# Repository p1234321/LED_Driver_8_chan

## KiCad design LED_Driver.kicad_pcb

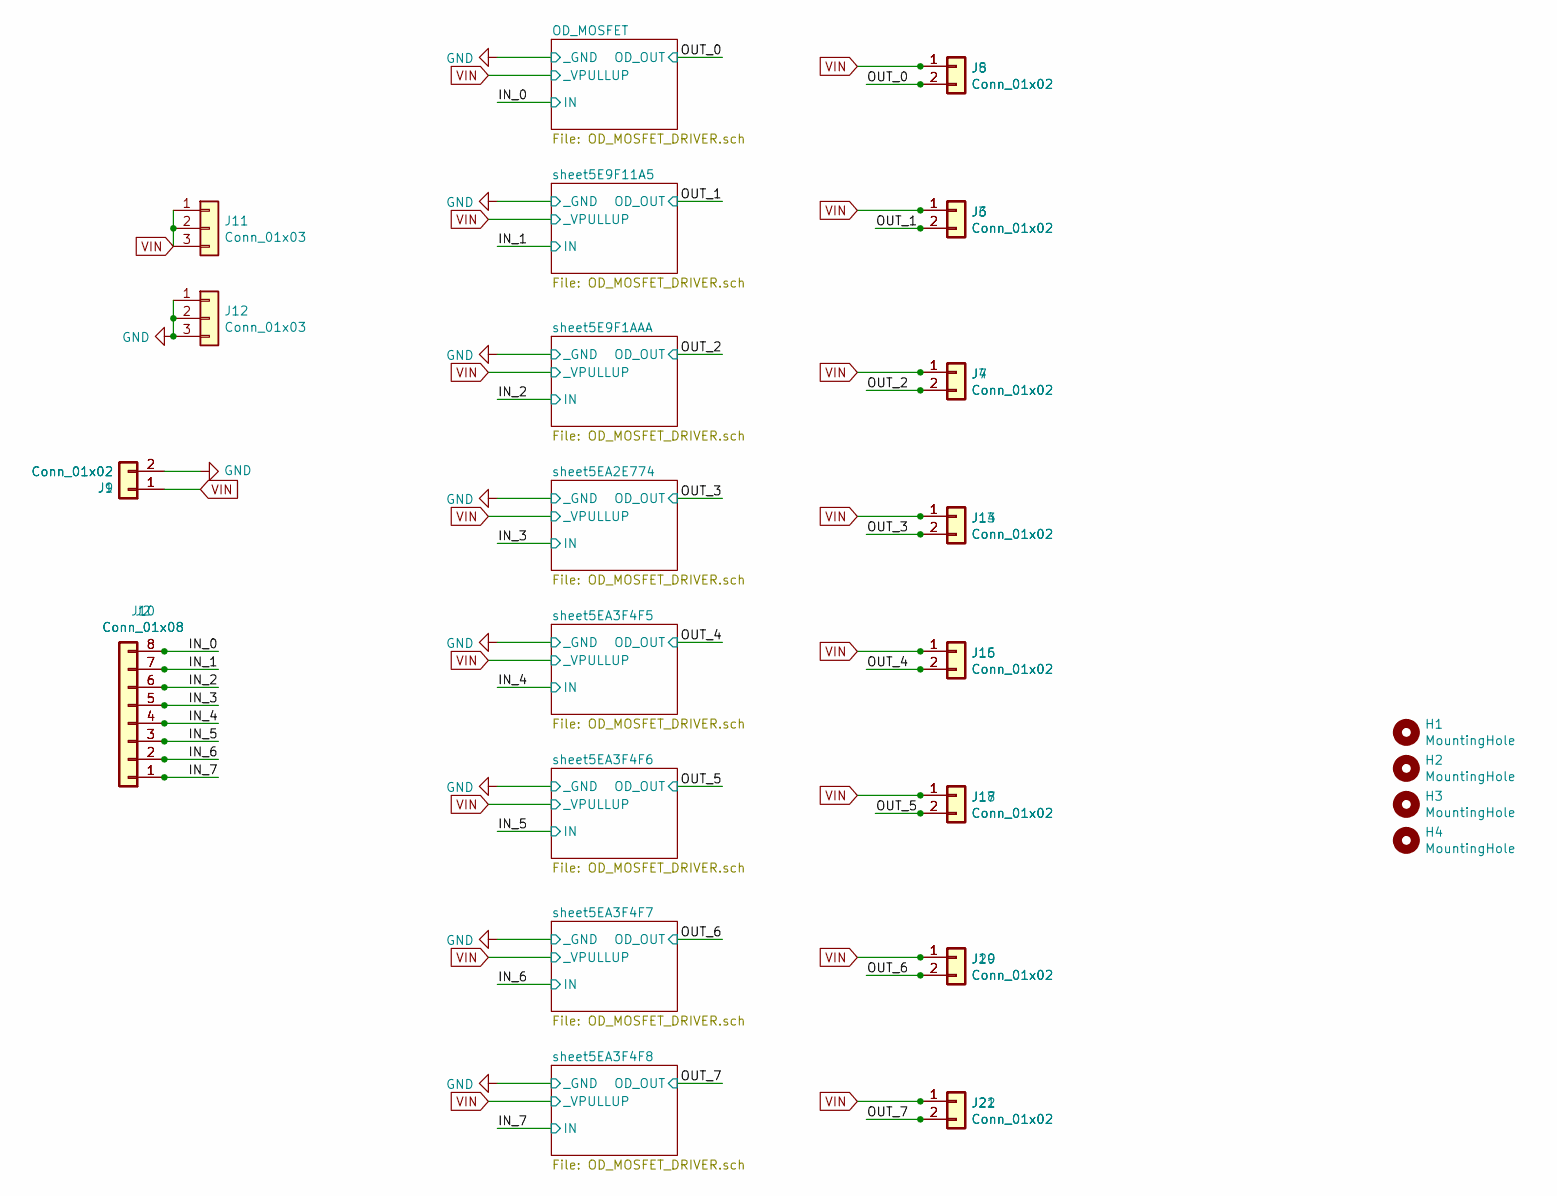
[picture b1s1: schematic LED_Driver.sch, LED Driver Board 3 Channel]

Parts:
H1, H2, H3, H4: MountingHole; MountingHole_2.7mm
J1, J3, J4, J5, J13, J15, J17, J19, J21: Conn_01x02; TerminalBlock_Phoenix_MKDS-1,5-2-5.08_1x02_P5.08mm_Horizont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
J2, J10: Conn_01x08; PinHeader_1x08_P2.54mm_Vertical
J6, J7, J8, J9, J14, J16, J18, J20, J22: Conn_01x02; KF2510-A-2P-M-TH-V
J11, J12: Conn_01x03; PinHeader_1x03_P2.54mm_Vertical

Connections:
/IN_0: J2.8, J10.8; also elsewhere on the board
/IN_1: J2.7, J10.7; also elsewhere on the board
/IN_2: J2.6, J10.6; also elsewhere on the board
/IN_3: J2.5, J10.5; also elsewhere on the board
/IN_4: J2.4, J10.4; also elsewhere on the board
/IN_5: J2.3, J10.3; also elsewhere on the board
/IN_6: J2.2, J10.2; also elsewhere on the board
/IN_7: J2.1, J10.1; also elsewhere on the board
/OUT_0: J5.2, J8.2; also elsewhere on the board
/OUT_1: J3.2, J6.2; also elsewhere on the board
/OUT_2: J4.2, J7.2; also elsewhere on the board
/OUT_3: J13.2, J14.2; also elsewhere on the board
/OUT_4: J15.2, J16.2; also elsewhere on the board
/OUT_5: J17.2, J18.2; also elsewhere on the board
/OUT_6: J19.2, J20.2; also elsewhere on the board
/OUT_7: J21.2, J22.2; also elsewhere on the board
GND: J1.2, J9.2, J12.1, J12.2, J12.3; also elsewhere on the board
VIN: J1.1, J3.1, J4.1, J5.1, J6.1, J7.1, J8.1, J9.1, J11.1, J11.2, J11.3, J13.1, J14.1, J15.1, J16.1, J17.1, J18.1, J19.1, J20.1, J21.1, J22.1; also elsewhere on the board

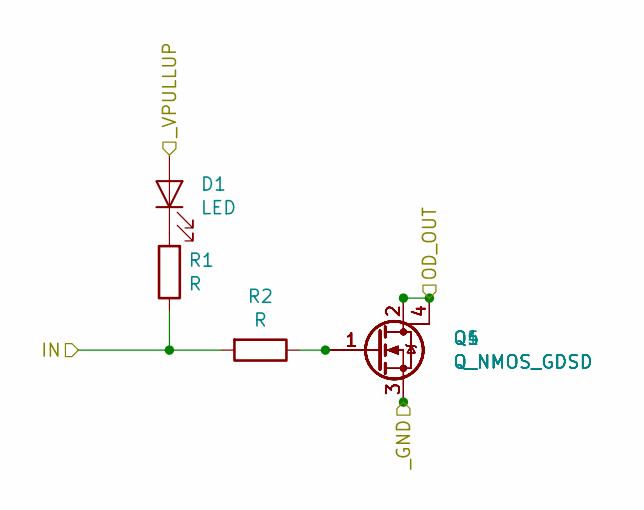
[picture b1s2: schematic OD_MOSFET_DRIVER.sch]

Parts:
D1: LED; LED_0805_2012Metric_Pad1.15x1.40mm_HandSolder
Q1: Q_NMOS_GDSD; TO-252-3_TabPin4
Q4: Q_NMOS_GDSD; SOT-223-3_TabPin2
Q5: Q_NMOS_GDSD; SOT-23_Handsoldering
R1, R2: R; R_0805_2012Metric_Pad1.15x1.40mm_HandSolder

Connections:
/IN_0: R1.1, R2.2; also elsewhere on the board
/OUT_0: Q1.2 (D), Q1.4 (D), Q4.2 (D), Q4.4 (D), Q5.2 (D), Q5.4 (D); also elsewhere on the board
GND: Q1.3 (S), Q4.3 (S), Q5.3 (S); also elsewhere on the board
unnamed: D1.1 (K), R1.2
unnamed: Q1.1 (G), Q4.1 (G), Q5.1 (G), R2.1
VIN: D1.2 (A); also elsewhere on the board

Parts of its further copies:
D2, D3, D4, D5, D6, D7, D8: LED; LED_0805_2012Metric_Pad1.15x1.40mm_HandSolder
Q2, Q3, Q10, Q13, Q16, Q19, Q22: Q_NMOS_GDSD; TO-252-3_TabPin4
Q6, Q8, Q11, Q14, Q17, Q20, Q23: Q_NMOS_GDSD; SOT-223-3_TabPin2
Q7, Q9, Q12, Q15, Q18, Q21, Q24: Q_NMOS_GDSD; SOT-23_Handsoldering
R3, R4, R5, R6, R7, R8, R9, R10, R11, R12, R13, R14, R15, R16: R; R_0805_2012Metric_Pad1.15x1.40mm_HandSolder

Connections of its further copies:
/IN_1: R3.1, R4.2; also elsewhere on the board
/IN_2: R5.1, R6.2; also elsewhere on the board
/IN_3: R7.1, R8.2; also elsewhere on the board
/IN_4: R9.1, R10.2; also elsewhere on the board
/IN_5: R11.1, R12.2; also elsewhere on the board
/IN_6: R13.1, R14.2; also elsewhere on the board
/IN_7: R15.1, R16.2; also elsewhere on the board
/OUT_1: Q2.2 (D), Q2.4 (D), Q6.2 (D), Q7.2 (D); also elsewhere on the board
/OUT_2: Q3.2 (D), Q3.4 (D), Q8.2 (D), Q9.2 (D); also elsewhere on the board
/OUT_3: Q10.2 (D), Q10.4 (D), Q11.2 (D), Q12.2 (D); also elsewhere on the board
/OUT_4: Q13.2 (D), Q13.4 (D), Q14.2 (D), Q15.2 (D); also elsewhere on the board
/OUT_5: Q16.2 (D), Q16.4 (D), Q17.2 (D), Q18.2 (D); also elsewhere on the board
/OUT_6: Q19.2 (D), Q19.4 (D), Q20.2 (D), Q21.2 (D); also elsewhere on the board
/OUT_7: Q22.2 (D), Q22.4 (D), Q23.2 (D), Q24.2 (D); also elsewhere on the board
GND: Q2.3 (S), Q3.3 (S), Q6.3 (S), Q7.3 (S), Q8.3 (S), Q9.3 (S), Q10.3 (S), Q11.3 (S), Q12.3 (S), Q13.3 (S), Q14.3 (S), Q15.3 (S), Q16.3 (S), Q17.3 (S), Q18.3 (S), Q19.3 (S), Q20.3 (S), Q21.3 (S), Q22.3 (S), Q23.3 (S), Q24.3 (S); also elsewhere on the board
unnamed: D2.1 (K), R3.2
unnamed: D3.1 (K), R5.2
unnamed: D4.1 (K), R7.2
unnamed: D5.1 (K), R9.2
unnamed: D6.1 (K), R11.2
unnamed: D7.1 (K), R13.2
unnamed: D8.1 (K), R15.2
unnamed: Q2.1 (G), Q6.1 (G), Q7.1 (G), R4.1
unnamed: Q3.1 (G), Q8.1 (G), Q9.1 (G), R6.1
unnamed: Q10.1 (G), Q11.1 (G), Q12.1 (G), R8.1
unnamed: Q13.1 (G), Q14.1 (G), Q15.1 (G), R10.1
unnamed: Q16.1 (G), Q17.1 (G), Q18.1 (G), R12.1
unnamed: Q19.1 (G), Q20.1 (G), Q21.1 (G), R14.1
unnamed: Q22.1 (G), Q23.1 (G), Q24.1 (G), R16.1
VIN: D2.2 (A), D3.2 (A), D4.2 (A), D5.2 (A), D6.2 (A), D7.2 (A), D8.2 (A); also elsewhere on the board

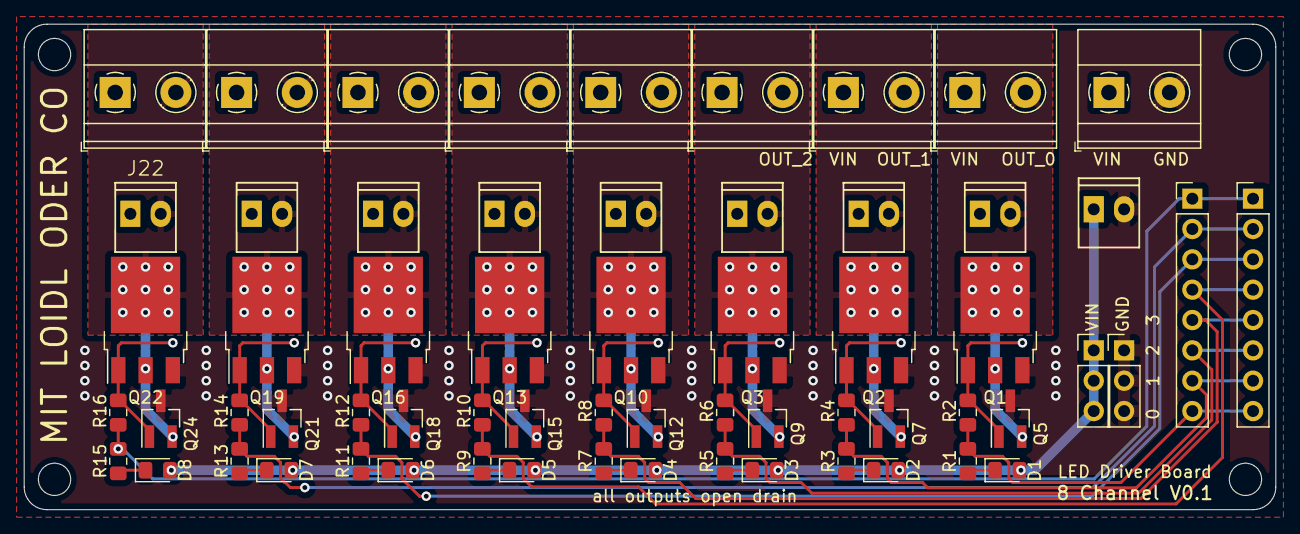
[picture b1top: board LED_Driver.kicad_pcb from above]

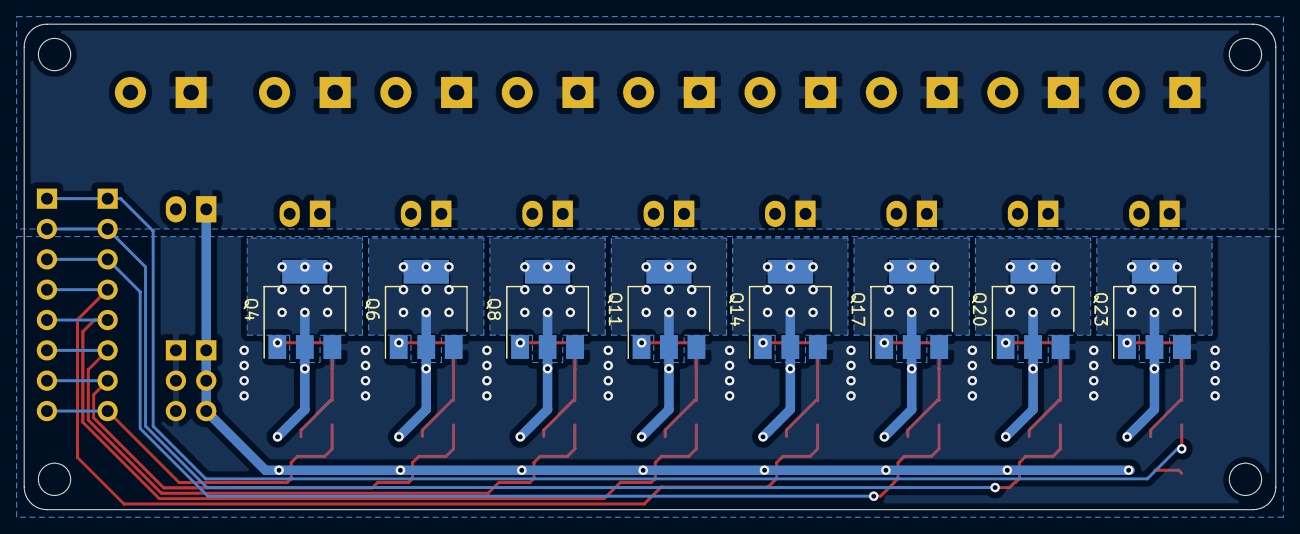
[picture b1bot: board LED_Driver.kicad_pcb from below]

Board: 2 copper layers, 104.8 x 40.6 mm, 74 parts (8 on the bottom side), 34 nets.

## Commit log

2023-05-07 added the files
